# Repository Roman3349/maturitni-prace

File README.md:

# maturitni-prace
Repozitář pro maturitní práci z informatiky

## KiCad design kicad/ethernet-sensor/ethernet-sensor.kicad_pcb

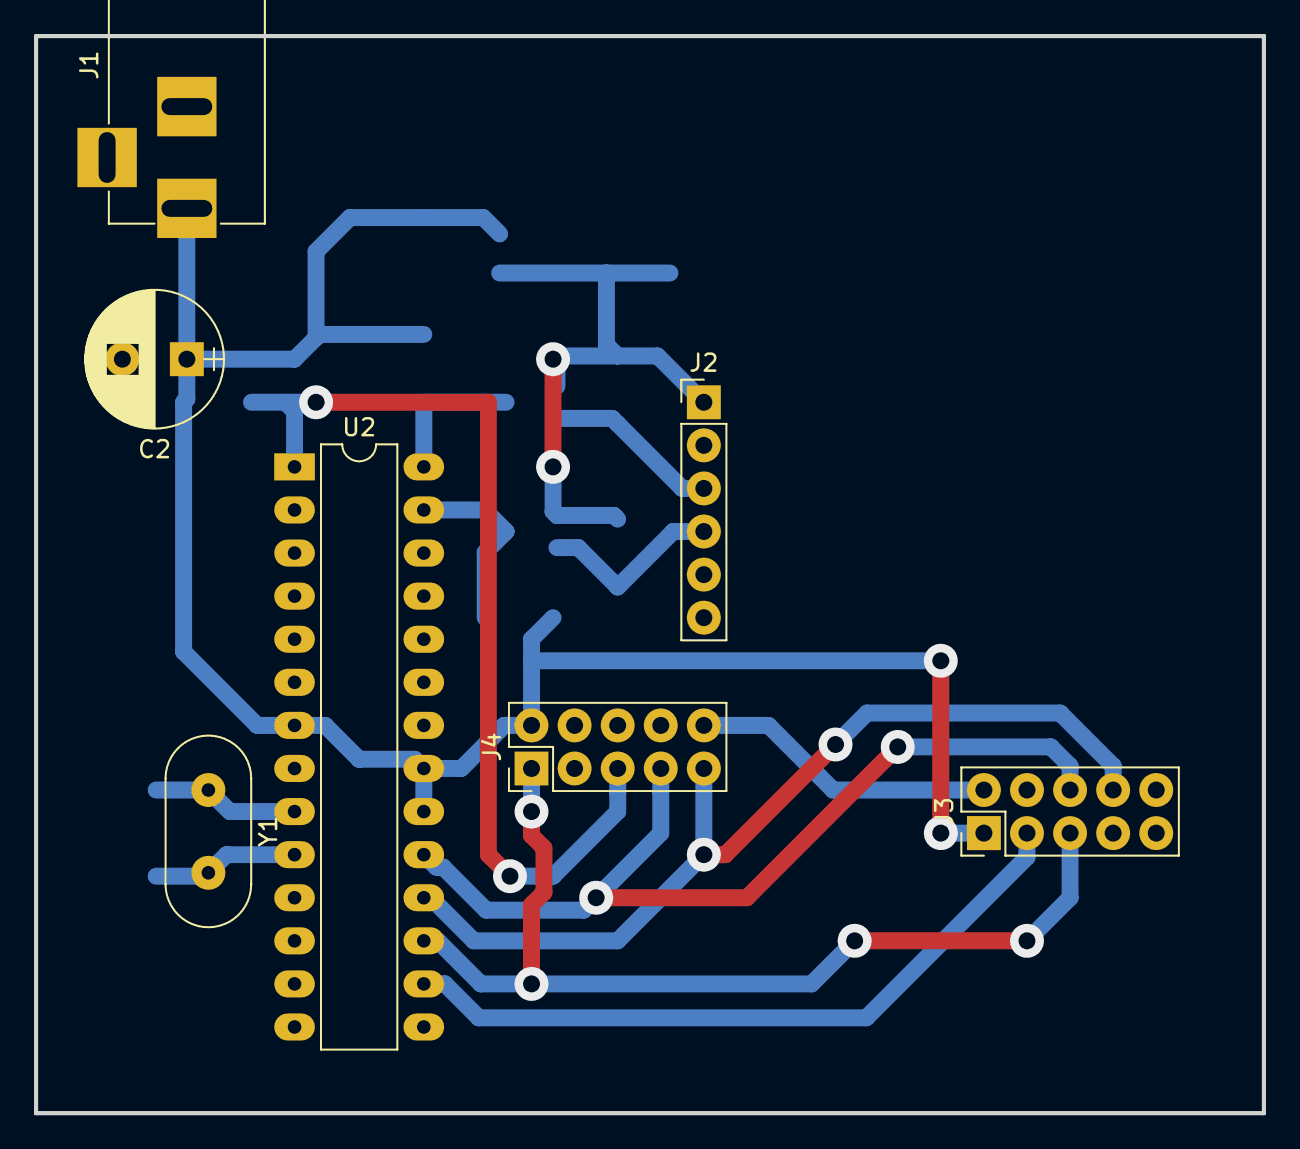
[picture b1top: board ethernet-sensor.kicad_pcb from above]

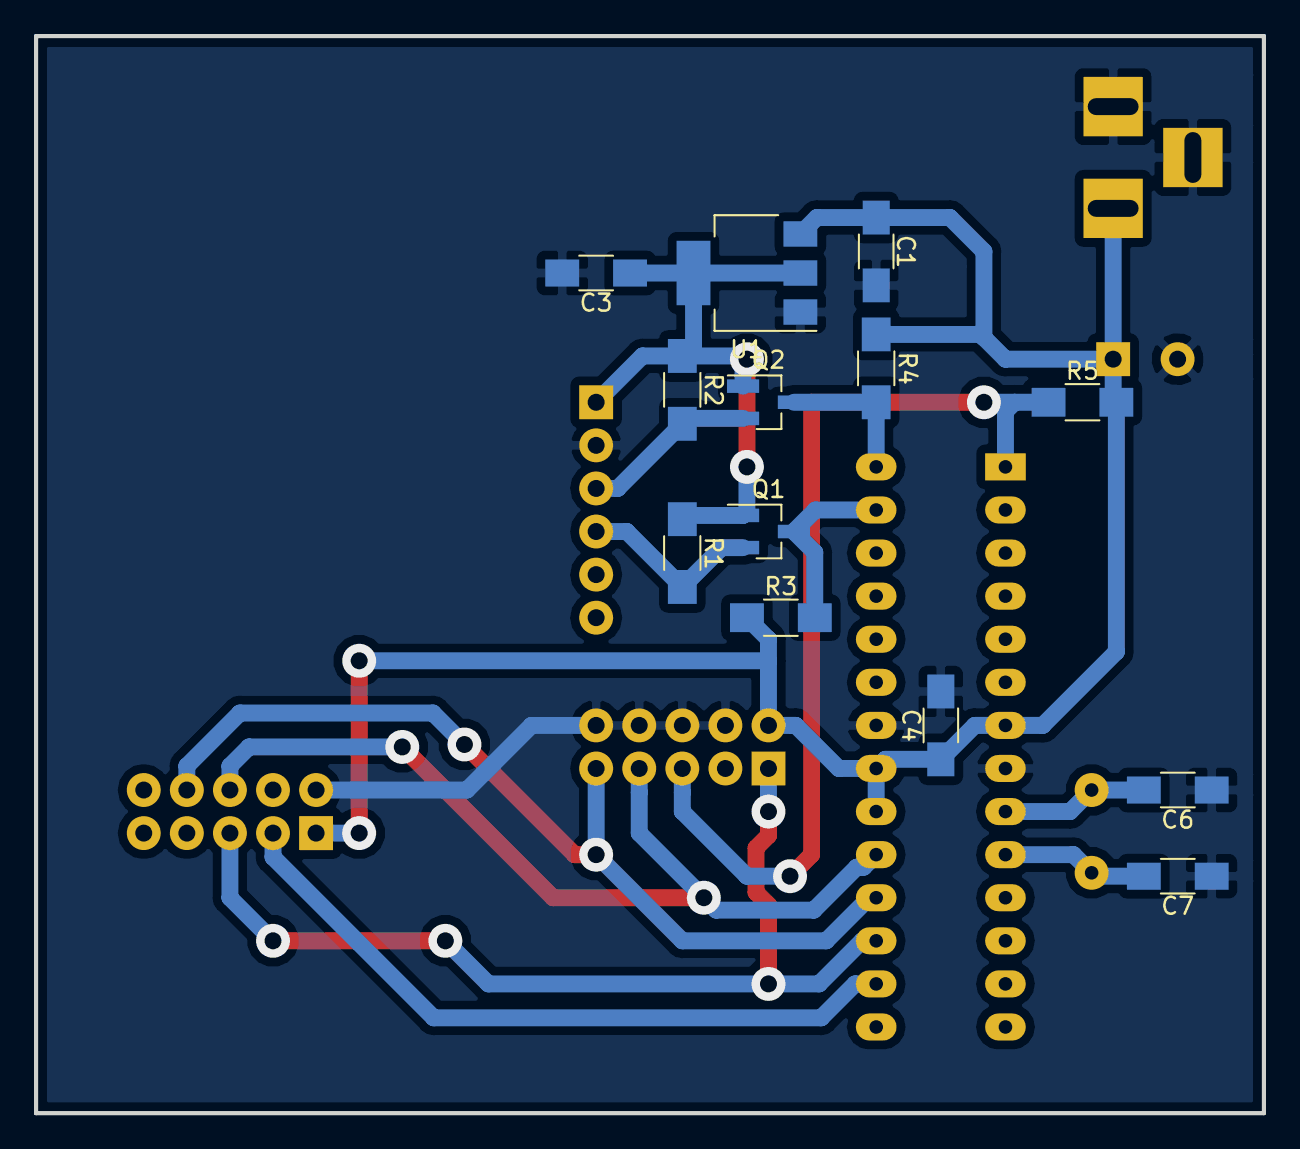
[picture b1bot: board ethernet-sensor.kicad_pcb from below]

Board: 2 copper layers, 72.4 x 63.5 mm, 20 parts (13 on the bottom side), 14 nets.

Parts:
C1, C3, C4: 100n; C_1206_HandSoldering
C2: 470uF; CP_Radial_D8.0mm_P3.80mm
C6, C7: 18p; C_1206_HandSoldering
J1: Barrel_Jack; BARREL_JACK
J2: Conn_BME280; Pin_Header_Straight_1x06_Pitch2.54mm
J3: Conn_W5100; Pin_Header_Straight_2x05_Pitch2.54mm
J4: AVR-ISP-10; Pin_Header_Straight_2x05_Pitch2.54mm
Q1, Q2: BSS138; SOT-23_Handsoldering
R1, R2, R3, R4, R5: 10k; R_1206_HandSoldering
U1: NCP1117-3.3_SOT223; SOT-223-3_TabPin2
U2: ATmega328P-PU; DIP-28_W7.62mm_LongPads
Y1: 16MHz; Crystal_HC49-U_Vertical

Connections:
+3V3: C3.1, J2.1, Q1.1, Q2.1, R1.1, R2.1, U1.2
+5V: C1.1, C2.1, C4.1, J1.1, J3.1, J4.2, R3.1, R4.1, R5.2, U1.3, U2.7, U2.20, U2.21
GND: C1.2, C2.2, C3.2, C4.2, C6.1, C7.1, J1.2, J1.3, J2.2, J3.2, J4.4, J4.6, J4.8, J4.10, U1.1, U2.8, U2.22
MISO: J3.8, J4.9, U2.18
MOSI: J3.5, J4.1, U2.17
unnamed: C6.2, U2.9, Y1.1
unnamed: C7.2, U2.10, Y1.2
RESET: J4.5, R5.1, U2.1
SCK: J3.6, J4.7, U2.19
SCL_Hi: Q2.3, R4.2, U2.28
SCL_Lo: J2.3, Q2.2, R2.2
SDA_Hi: Q1.3, R3.2, U2.27
SDA_Lo: J2.4, Q1.2, R1.2
SS: J3.3, U2.16

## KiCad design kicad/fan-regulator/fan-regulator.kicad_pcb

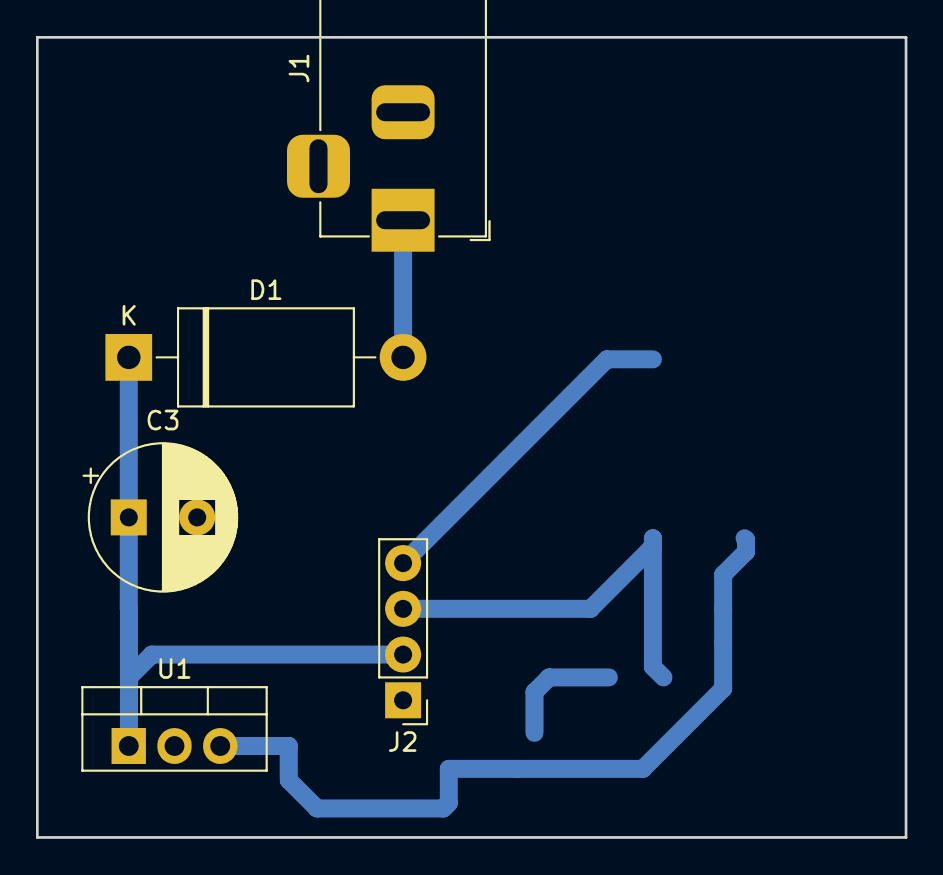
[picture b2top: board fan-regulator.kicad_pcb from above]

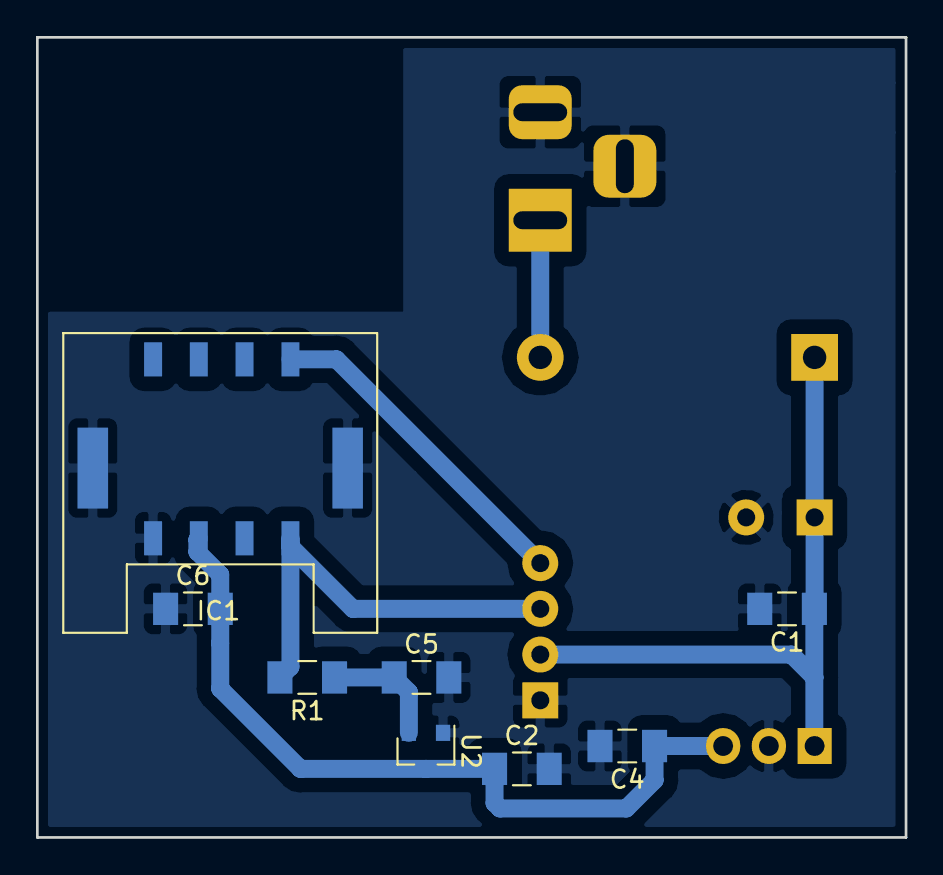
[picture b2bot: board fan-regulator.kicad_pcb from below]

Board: 2 copper layers, 48.3 x 44.4 mm, 13 parts (8 on the bottom side), 7 nets.

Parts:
C1, C2, C4, C5, C6: 100n; C_1206_3216Metric_Pad1.39x1.80mm_HandSolder
C3: CP; CP_Radial_D8.0mm_P3.80mm
D1: BY550-400; D_DO-201_P15.24mm_Horizontal
IC1: TR-72D; IQRF_TRx2DA_KON-SIM-01
J1: Barrel_Jack; BarrelJack_Horizontal
J2: Conn_01x04_Male; PinHeader_1x04_P2.54mm_Vertical
R1: 10k; R_1206_3216Metric_Pad1.39x1.80mm_HandSolder
U1: LM7805_TO220; TO-220-3_Vertical
U2: MCP1700-3002E_SOT23; SOT-23

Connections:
+3V3: C5.1, R1.1, U2.2
+5V: C2.1, C4.1, C6.2, IC1.3, U1.3, U2.3
+12V: C1.1, C3.1, D1.1, J2.2, U1.1
FAN_PWM: IC1.5, J2.4
FAN_SPEED: IC1.1, J2.3, R1.2
GND: C1.2, C2.2, C3.2, C4.2, C5.2, C6.1, IC1.4, IC1.9, J1.2, J1.3, J2.1, U1.2, U2.1
unnamed: D1.2, J1.1

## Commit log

2018-01-09 Add the first page of the documentation
2018-01-09 Modify format of the first page
2018-01-10 Add a skeleton of the documentation
2018-02-19 Add more information into the documentation
2018-04-24 Add schemas and PCBs
2018-04-26 Fix bugs in KiCAD EDA's files
2018-04-27 Add a source code for the Arduino Ethernet sensor
2018-04-27 Update source code for the Arduino Ethernet sensor
2018-04-28 Add source code for IQRF PWM fan regulator
2018-04-29 Add Node-RED flow
2018-04-29 Update Node-RED flow
2018-04-29 Update software for IQRF PWM fan controller
2018-04-29 Update the documentation
2018-04-30 Use a P regulator for a temperature regulation
2018-05-10 Fix typo in a documentation
2018-05-17 Fix coding style of Arduino Etherner sensor's source code
2018-05-17 Add Dockerfile for the gateway
2018-05-24 Add a presentation
2018-05-24 Fix a presentation
